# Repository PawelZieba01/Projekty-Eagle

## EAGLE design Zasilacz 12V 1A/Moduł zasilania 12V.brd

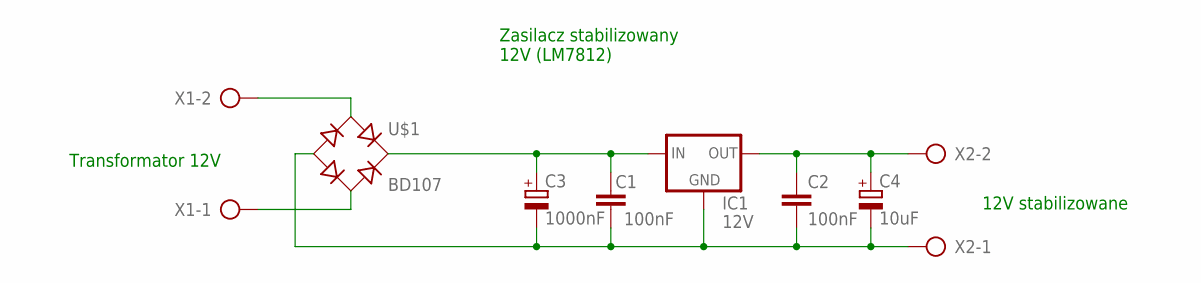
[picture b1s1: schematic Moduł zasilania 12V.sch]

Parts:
C1, C2: 100nF; C50-45-75
C3: 1000nF; E5-13
C4: 10uF; E2,5-6
IC1: 12V; 78XXS
U$1: BD107; B-DIL
X1, X2: AK300/2

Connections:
unnamed: U$1.AC1, X1.2
unnamed: U$1.AC2, X1.1
unnamed: C1.P$1 (1), C2.P$2 (2), C3.P$2 (-), C4.P$2 (-), IC1.GND, U$1.-, X2.1
unnamed: C1.P$2 (2), C3.P$1 (+), IC1.IN, U$1.+
unnamed: C2.P$1 (1), C4.P$1 (+), IC1.OUT, X2.2

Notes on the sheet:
Zasilacz stabilizowany 12V (LM7812)
Transformator 12V
12V stabilizowane

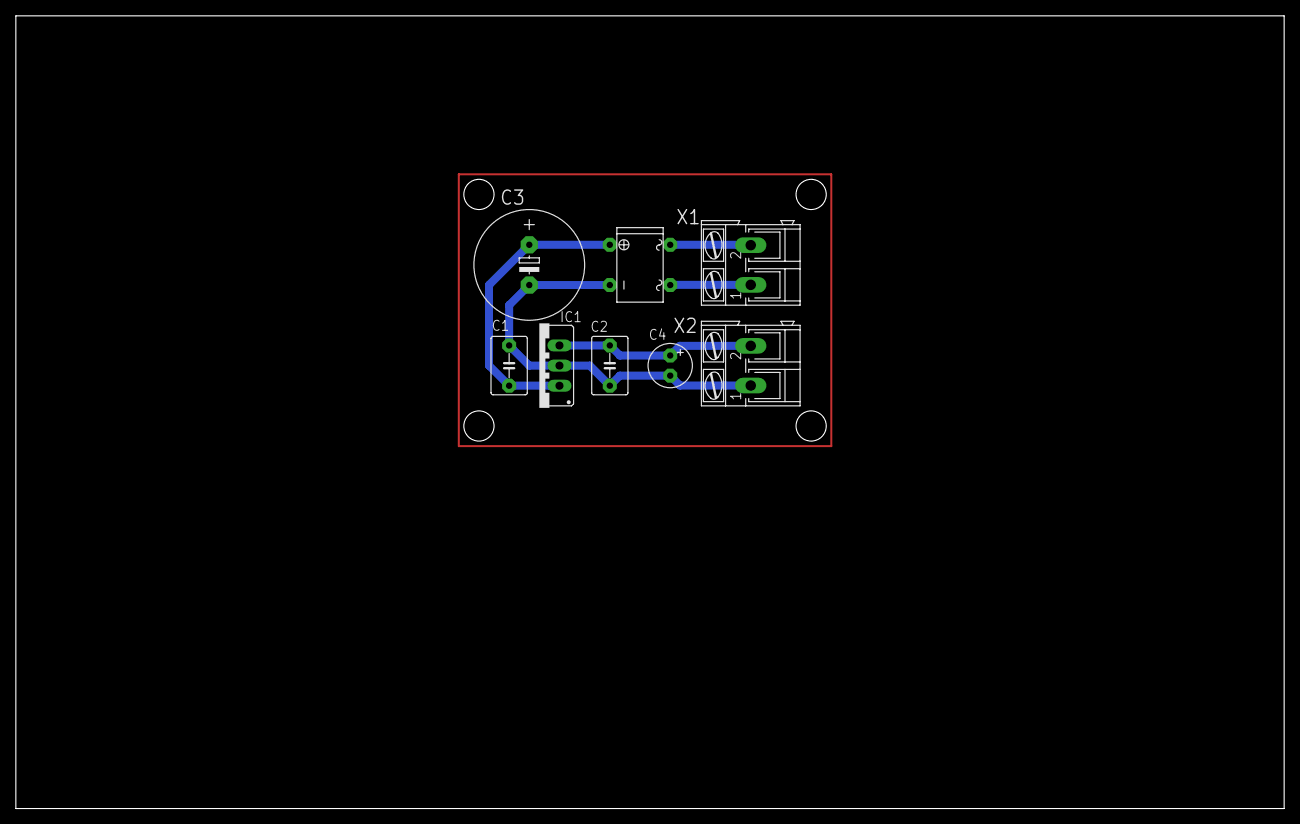
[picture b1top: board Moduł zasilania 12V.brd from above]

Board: 2 copper layers, 160.0 x 100.0 mm, 8 parts (0 on the bottom side), 5 nets.

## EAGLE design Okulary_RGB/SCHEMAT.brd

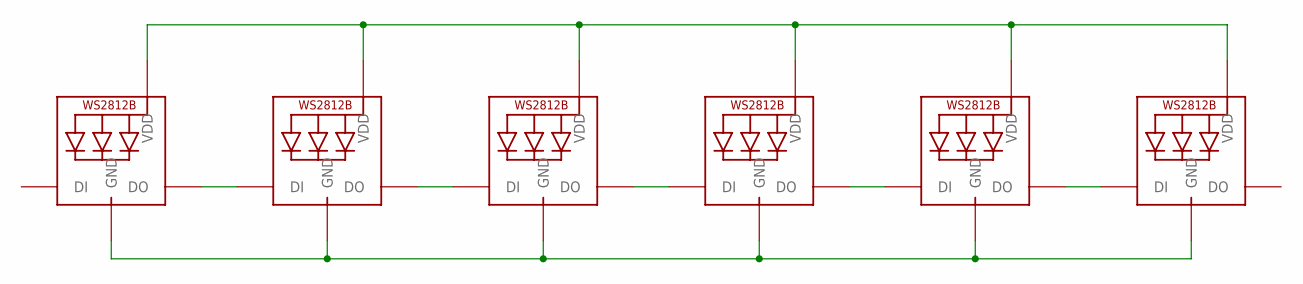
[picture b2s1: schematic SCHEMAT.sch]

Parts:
LED1, LED2, LED3, LED4, LED5, LED6: WS2812B5050; WS2812B

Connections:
unnamed: LED1.1-VDD (VDD), LED2.1-VDD (VDD), LED3.1-VDD (VDD), LED4.1-VDD (VDD), LED5.1-VDD (VDD), LED6.1-VDD (VDD)
unnamed: LED1.3-GND (GND), LED2.3-GND (GND), LED3.3-GND (GND), LED4.3-GND (GND), LED5.3-GND (GND), LED6.3-GND (GND)
unnamed: LED1.2-DOUT (DO), LED2.4-DIN (DI)
unnamed: LED2.2-DOUT (DO), LED3.4-DIN (DI)
unnamed: LED3.2-DOUT (DO), LED4.4-DIN (DI)
unnamed: LED4.2-DOUT (DO), LED5.4-DIN (DI)
unnamed: LED5.2-DOUT (DO), LED6.4-DIN (DI)

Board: 2 copper layers, 6 parts (3 on the bottom side), 7 nets, no tracks yet.

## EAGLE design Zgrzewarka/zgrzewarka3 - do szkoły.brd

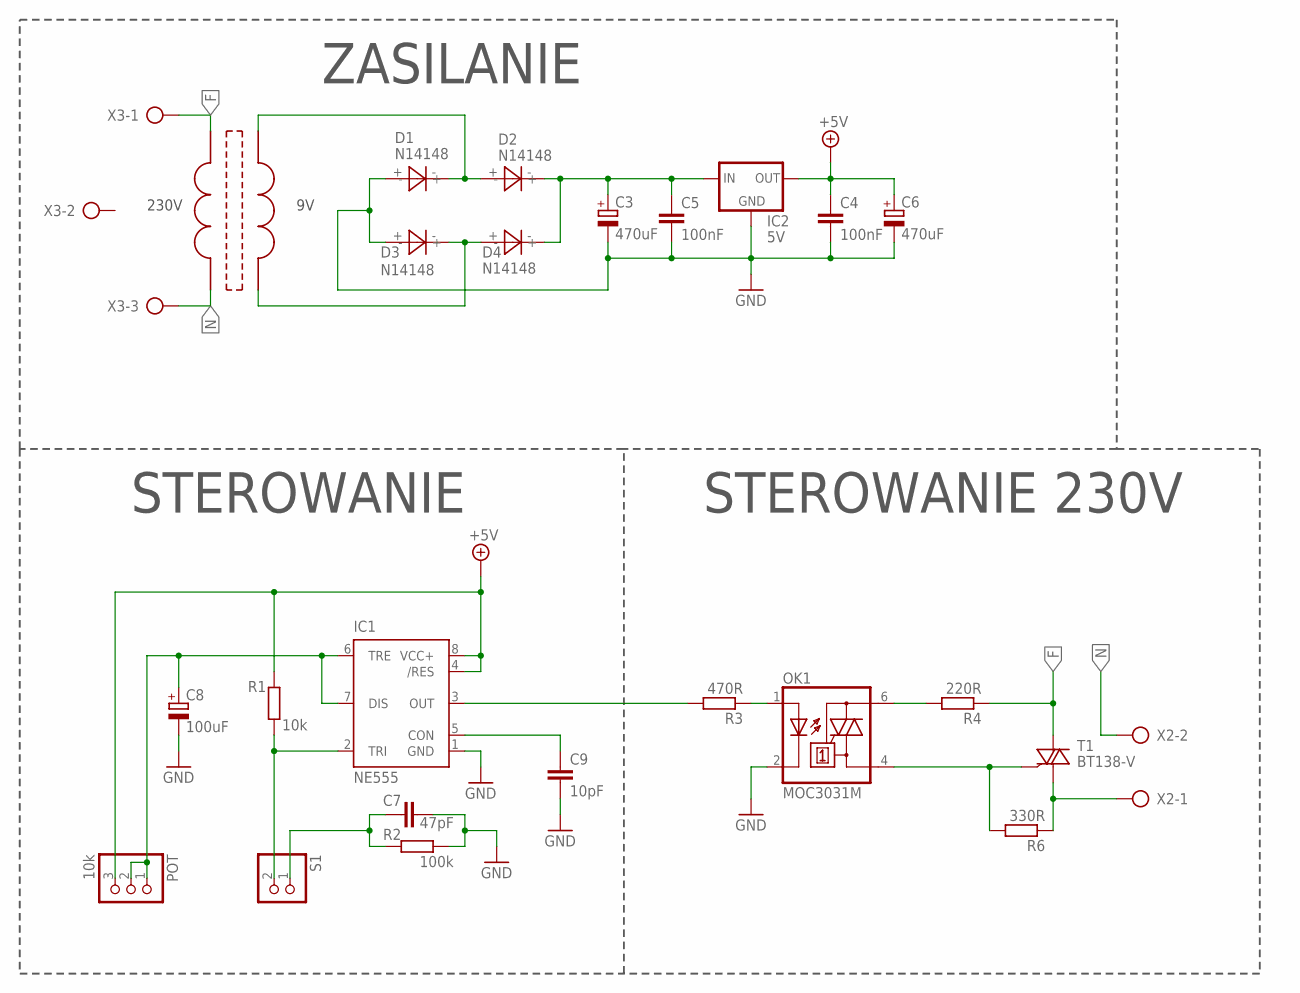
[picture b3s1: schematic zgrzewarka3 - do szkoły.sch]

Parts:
C3, C6: 470uF; C5-8,5
C4, C5: 100nF; C50-45-75
C7: 47pF; C50-45-75
C8: 100uF; C5-8,5
C9: 10pF; C50-45-75
D1, D2, D3, D4: N14148; DO35-7
IC1: NE555; DIL-08
IC2: 5V; 78LXX
OK1: MOC3031M; DIL06
POT: 10k; 1X03
R1: 10k; 204/7
R2: 100k; 204/7
R3: 470R; 204/7
R4: 220R; 204/7
R6: 330R; 204/7
S1: PINHD-1X2; 1X02
T1: BT138-V; TO220BV
U$1: TRAFO-9V; OBUDOWA1
X2: AK300/2
X3: AK300/3

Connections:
+5V: C4.P$1 (1), C6.+, IC1.4 (/RES), IC1.8 (VCC+), IC2.OUT, POT.3, R1.P$2 (2)
F: R4.P$1 (1), T1.T2 (A2), U$1.230V-1, X3.1
GND: C3.-, C4.P$2 (2), C5.P$2 (2), C6.-, C7.P$2 (2), C8.-, C9.P$2 (2), D1.+, D3.+, IC1.1 (GND), IC2.GND, OK1.2 (C), R2.P$1 (1)
N: U$1.230V-2, X2.2, X3.3
unnamed: C3.+, C5.P$1 (1), D2.-, D4.-, IC2.IN
unnamed: D1.-, D2.+, U$1.9V-1
unnamed: D3.-, D4.+, U$1.9V-2
unnamed: C9.P$1 (1), IC1.5 (CON)
unnamed: IC1.2 (TRI), R1.P$1 (1), S1.2
unnamed: IC1.3 (OUT), R3.P$2 (2)
unnamed: C7.P$1 (1), R2.P$2 (2), S1.1
unnamed: OK1.1 (A), R3.P$1 (1)
unnamed: C8.+, IC1.6 (TRE), IC1.7 (DIS), POT.1, POT.2
unnamed: OK1.6 (A2), R4.P$2 (2)
unnamed: OK1.4 (A1), R6.P$2 (2), T1.G
unnamed: R6.P$1 (1), T1.T1 (A1), X2.1

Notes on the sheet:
ZASILANIE
STEROWANIE
STEROWANIE 230V

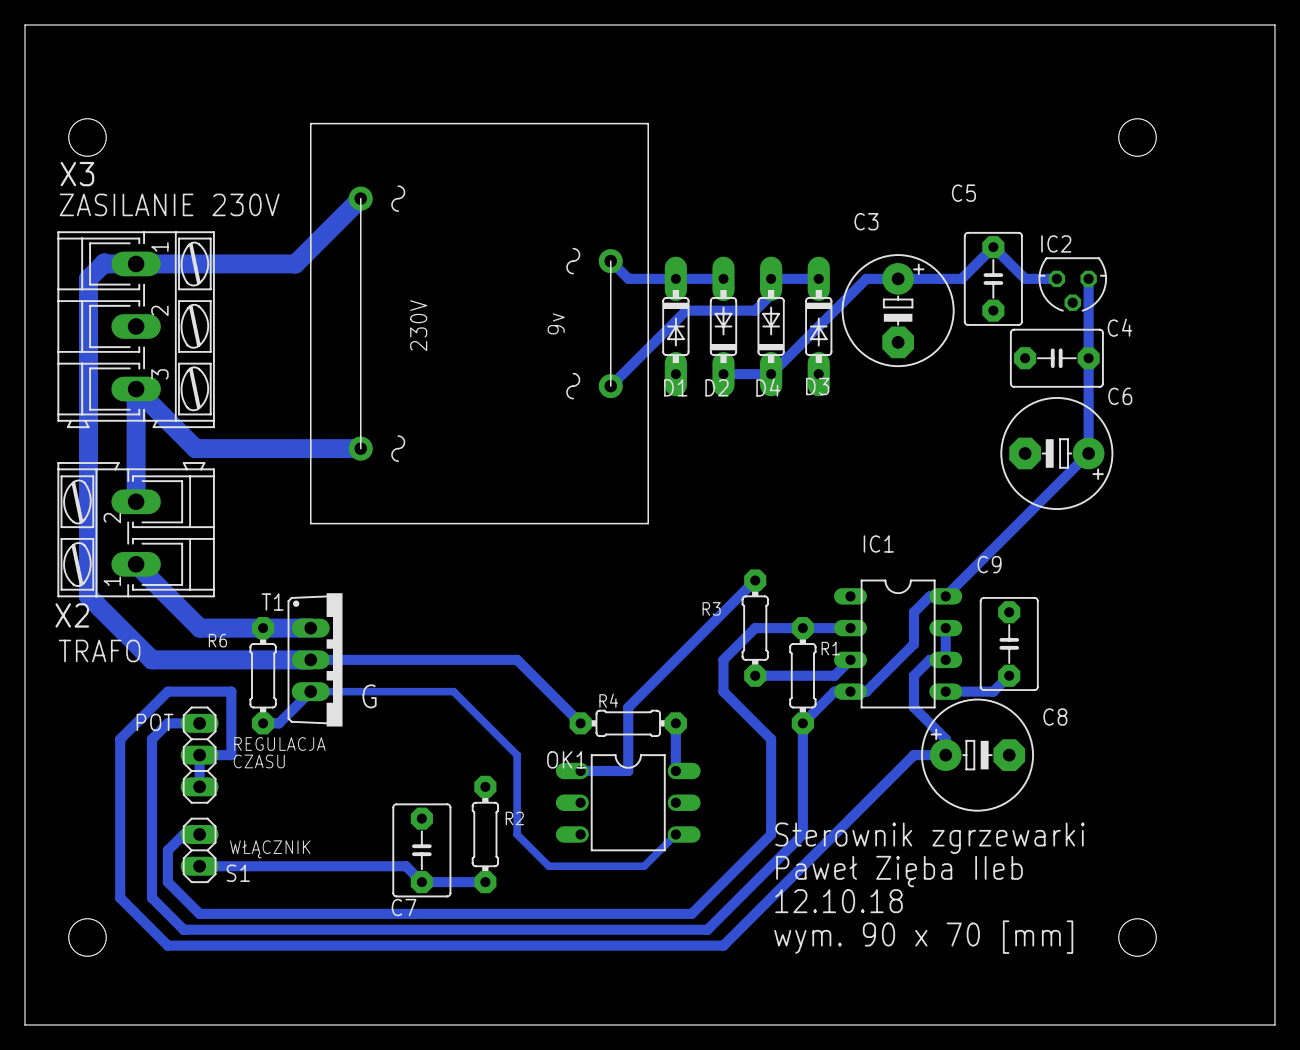
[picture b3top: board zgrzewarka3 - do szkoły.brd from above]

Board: 2 copper layers, 100.0 x 80.0 mm, 25 parts (0 on the bottom side), 16 nets.

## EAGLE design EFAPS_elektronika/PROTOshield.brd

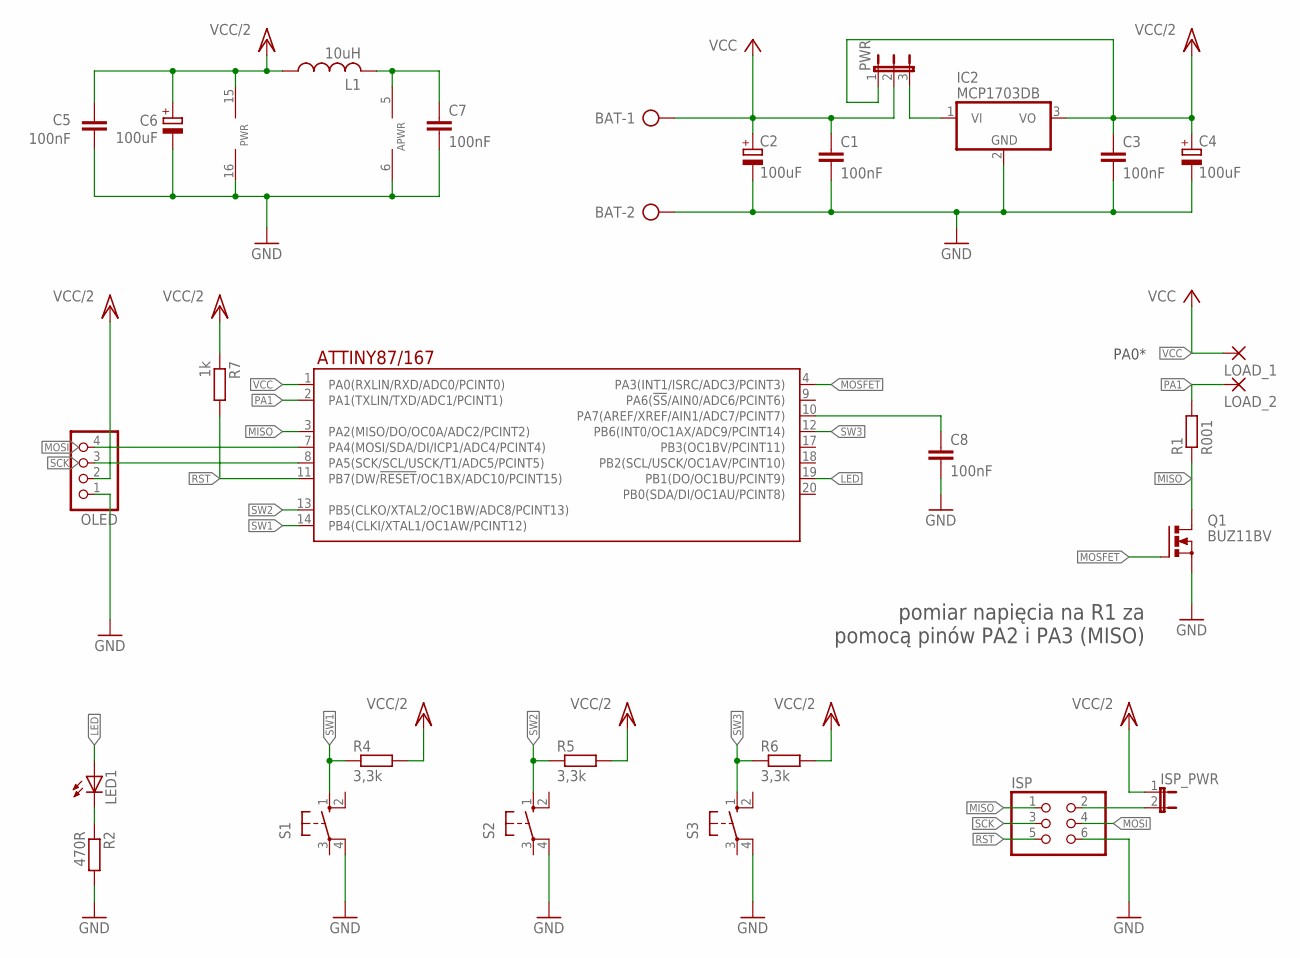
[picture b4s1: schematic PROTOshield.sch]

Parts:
BAT: AK300/2
C1, C3, C5, C7, C8: 100nF; C050-045X075
C2, C4, C6: 100uF; E3,5-8
IC2: MCP1703DB; SOT223
ISP: PINHD-2X3; 2X03
ISP_PWR: JP1E; JP1
L1: 10uH; 0207/7
LED1: LED5MM
LOAD_1, LOAD_2: 3,81/1,3
OLED: PINHD-1X4; 1X04
PWR: JP2E; JP2
Q1: BUZ11BV; TO220BV
R1: R001; R2512
R2: 470R; R1206
R4, R5, R6: 3,3k; R1206
R7: 1k; R1206
S1, S2, S3: 10-XX; B3F-10XX
U$1: ATTINY87/167; SOIC127P1032X265-20N

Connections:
GND: BAT.2, C1.2, C2.-, C3.2, C4.-, C5.2, C6.-, C7.2, C8.2, IC2.2 (GND), ISP.6, OLED.1, Q1.S, R2.2, S1.4 (P1), S2.4 (P1), S3.4 (P1), U$1.6 (AGND), U$1.16 (GND)
LED: LED1.A, U$1.19 (PB1(DO/OC1BU/PCINT9))
MISO: ISP.1, Q1.D, R1.1, U$1.3 (PA2(MISO/DO/OC0A/ADC2/PCINT2))
MOSFET: Q1.G, U$1.4 (PA3(INT1/ISRC/ADC3/PCINT3))
MOSI: ISP.4, OLED.4, U$1.7 (PA4(MOSI/SDA/DI/ICP1/ADC4/PCINT4))
unnamed: LED1.K (C), R2.1
unnamed: IC2.1 (VI), PWR.3
unnamed: ISP.2, ISP_PWR.2
unnamed: C8.1, U$1.10 (PA7(AREF/XREF/AIN1/ADC7/PCINT7))
unnamed: C7.1, L1.2, U$1.5 (AVCC)
PA1: LOAD_2.1, R1.2, U$1.2 (PA1(TXLIN/TXD/ADC1/PCINT1))
RST: ISP.5, R7.2, U$1.11 (PB7(DW/!RESET!/OC1BX/ADC10/PCINT15))
SCK: ISP.3, OLED.3, U$1.8 (PA5(SCK/SCL/USCK/T1/ADC5/PCINT5))
SW1: R4.1, S1.1 (S), U$1.14 (PB4(CLKI/XTAL1/OC1AW/PCINT12))
SW2: R5.1, S2.1 (S), U$1.13 (PB5(CLKO/XTAL2/OC1BW/ADC8/PCINT13))
SW3: R6.1, S3.1 (S), U$1.12 (PB6(INT0/OC1AX/ADC9/PCINT14))
VCC: BAT.1, C1.1, C2.+, LOAD_1.1, PWR.2, U$1.1 (PA0(RXLIN/RXD/ADC0/PCINT0))
VCC/2: C3.1, C4.+, C5.1, C6.+, IC2.3 (VO), ISP_PWR.1, L1.1, OLED.2, PWR.1, R4.2, R5.2, R6.2, R7.1, U$1.15 (VCC)

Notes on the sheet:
PA0*
pomiar napięcia na R1 za pomocą pinów PA2 i PA3 (MISO)

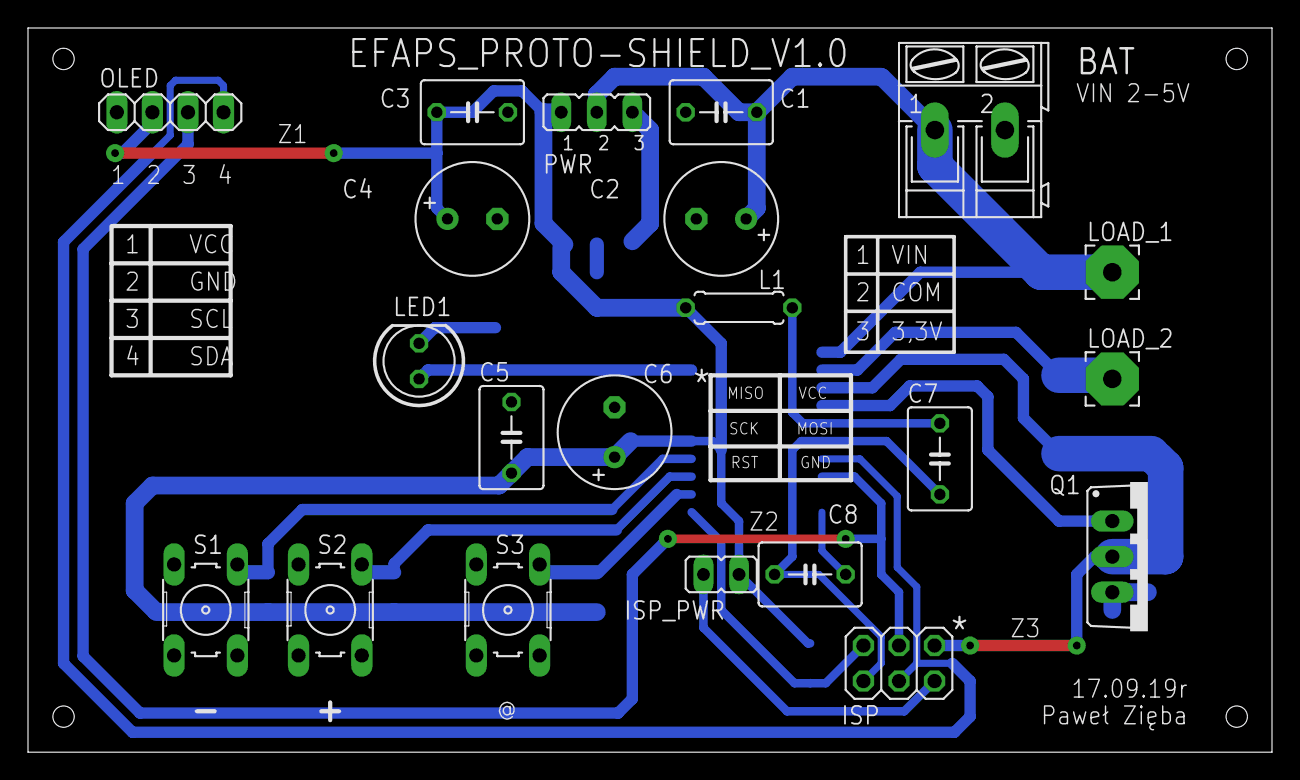
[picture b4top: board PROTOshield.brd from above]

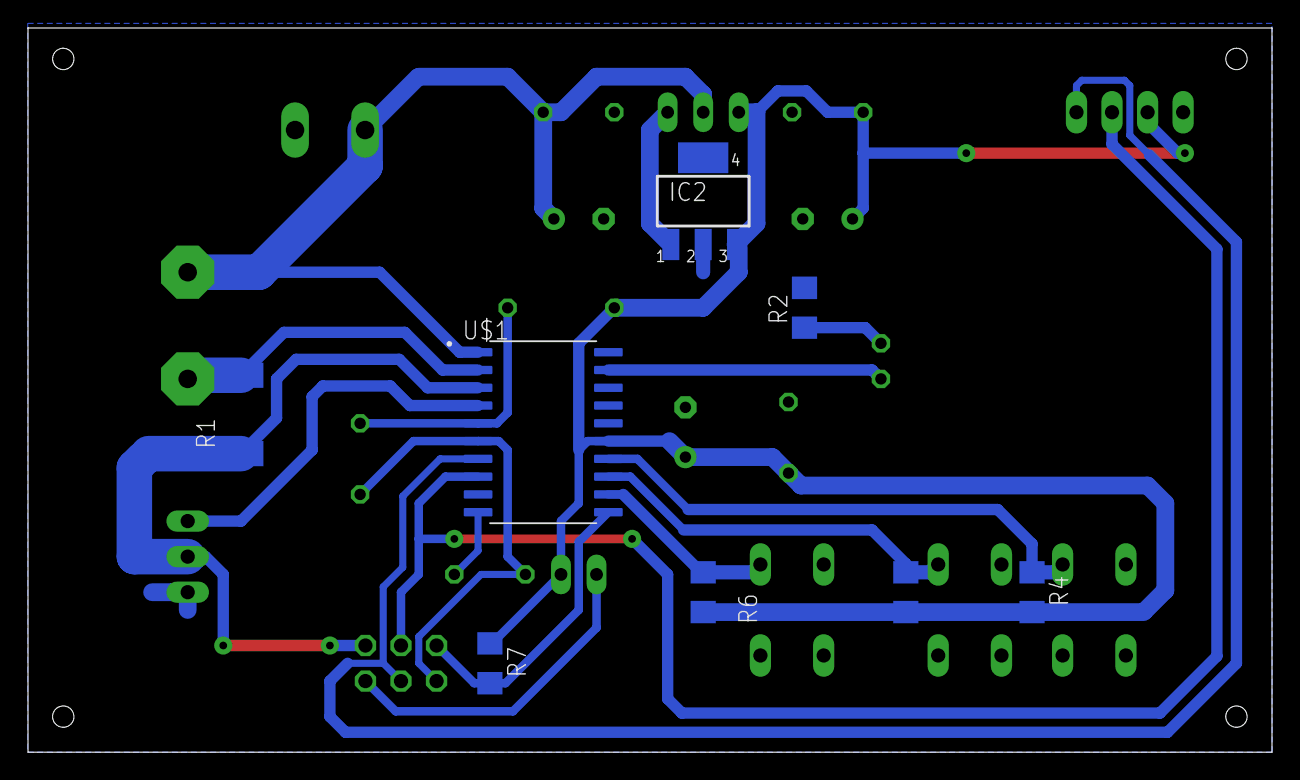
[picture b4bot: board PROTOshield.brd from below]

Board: 2 copper layers, 88.9 x 51.7 mm, 29 parts (8 on the bottom side), 18 nets.

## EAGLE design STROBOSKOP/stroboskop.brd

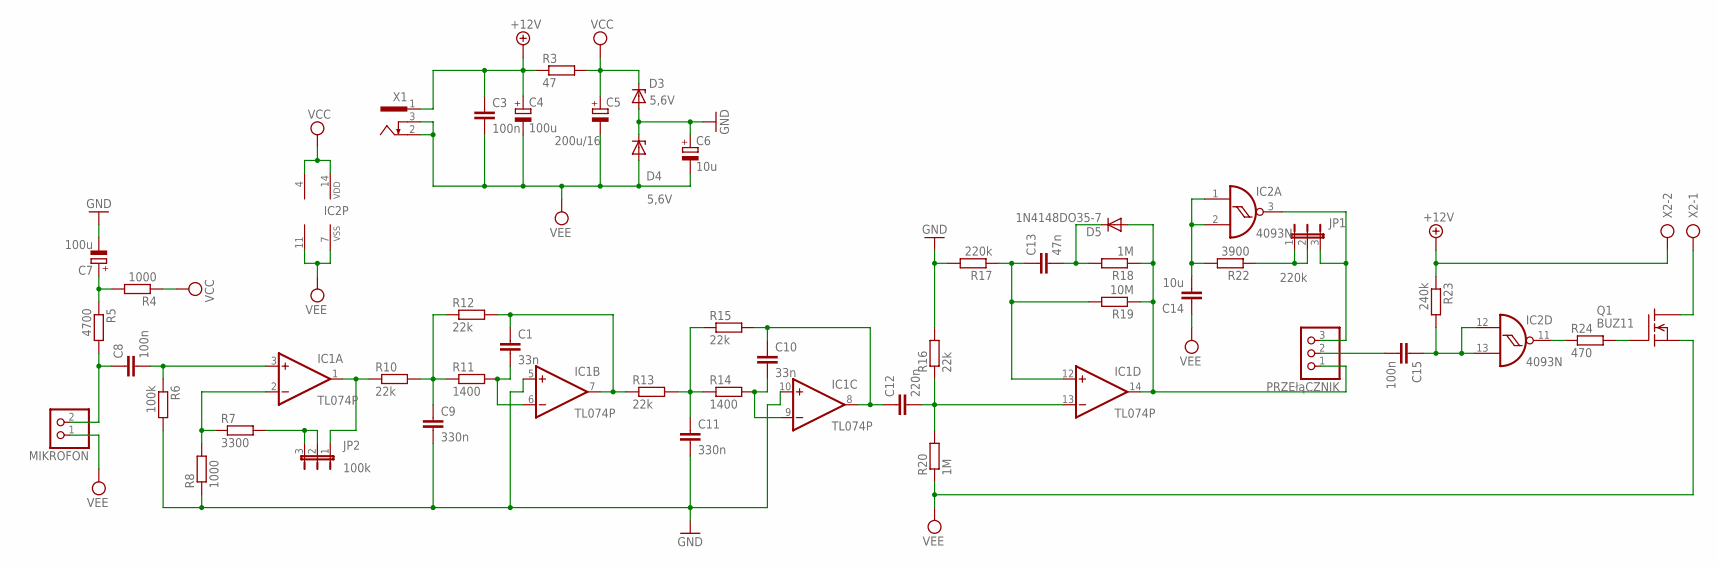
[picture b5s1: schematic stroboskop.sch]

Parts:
C1, C10: 33n; C025-025X050
C3, C8, C15: 100n; C025-025X050
C4, C7: 100u; E2,5-6E
C5: 200u/16; E2,5-6E
C6: 10u; E2,5-6E
C9, C11: 330n; C025-025X050
C12: 220n; C025-025X050
C13: 47n; C025-025X050
C14: 10u; C025-025X050
D3, D4: 5,6V; DO35Z10
D5: 1N4148DO35-7; DO35-7
IC1: TL074P; DIL14
IC2: 4093N; DIL14
JP1: 220k; JP2
JP2: 100k; JP2
MIKROFON: PINHD-1X2; 1X02
PRZEłąCZNIK: PINHD-1X3; 1X03
Q1: BUZ11; TO220
R3: 47; 0204/5
R4, R8: 1000; 0204/5
R5: 4700; 0204/5
R6: 100k; 0204/5
R7: 3300; 0204/5
R10, R12, R13, R15, R16: 22k; 0204/5
R11, R14: 1400; 0204/5
R17: 220k; 0204/5
R18, R20: 1M; 0204/5
R19: 10M; 0204/5
R22: 3900; 0204/5
R23: 240k; 0204/5
R24: 470; 0204/5
X1: 733980-62
X2: AK300/2

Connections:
+12V: C3.1, C4.+, R3.1, R23.1, X1.1, X2.2
GND: C6.+, C7.-, C9.2, C11.2, D3.A, D4.C, IC1.5 (+IN), IC1.10 (+IN), R6.2, R8.1, R16.2, R17.2
unnamed: C7.+, R4.2, R5.1
unnamed: C8.1, MIKROFON.2, R5.2
unnamed: C8.2, IC1.3 (+IN), R6.1
unnamed: C11.1, R13.2, R14.1, R15.1
unnamed: IC1.2 (-IN), R7.1, R8.2
unnamed: C10.2, IC1.9 (-IN), R14.2
unnamed: JP2.2, JP2.3, R7.2
unnamed: C10.1, C12.1, IC1.8 (OUT), R15.2
unnamed: IC1.1 (OUT), JP2.1, R10.1
unnamed: C9.1, R10.2, R11.1, R12.1
unnamed: C1.1, IC1.7 (OUT), R12.2, R13.1
unnamed: C1.2, IC1.6 (-IN), R11.2
unnamed: C12.2, IC1.13 (-IN), R16.1, R20.2
unnamed: C15.2, PRZEłąCZNIK.2
unnamed: C13.1, IC1.12 (+IN), R17.1, R19.2
unnamed: C13.2, D5.C, R18.2
unnamed: D5.A, IC1.14 (OUT), PRZEłąCZNIK.1, R18.1, R19.1
unnamed: IC2.3 (O), JP1.3, PRZEłąCZNIK.3
unnamed: C15.1, IC2.12 (I0), IC2.13 (I1), R23.2
unnamed: C14.2, IC2.1 (I0), IC2.2 (I1), R22.2
unnamed: IC2.11 (O), R24.1
unnamed: JP1.1, JP1.2, R22.1
unnamed: Q1.1 (G), R24.2
unnamed: Q1.2 (D), X2.1
VCC: C5.+, D3.C, IC1.4 (V+), IC2.14 (VDD), R3.2, R4.1
VEE: C3.2, C4.-, C5.-, C6.-, C14.1, D4.A, IC1.11 (V-), IC2.7 (VSS), MIKROFON.1, Q1.3 (S), R20.1, X1.2, X1.3

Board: 2 copper layers, 46 parts (0 on the bottom side), 28 nets, no tracks yet.

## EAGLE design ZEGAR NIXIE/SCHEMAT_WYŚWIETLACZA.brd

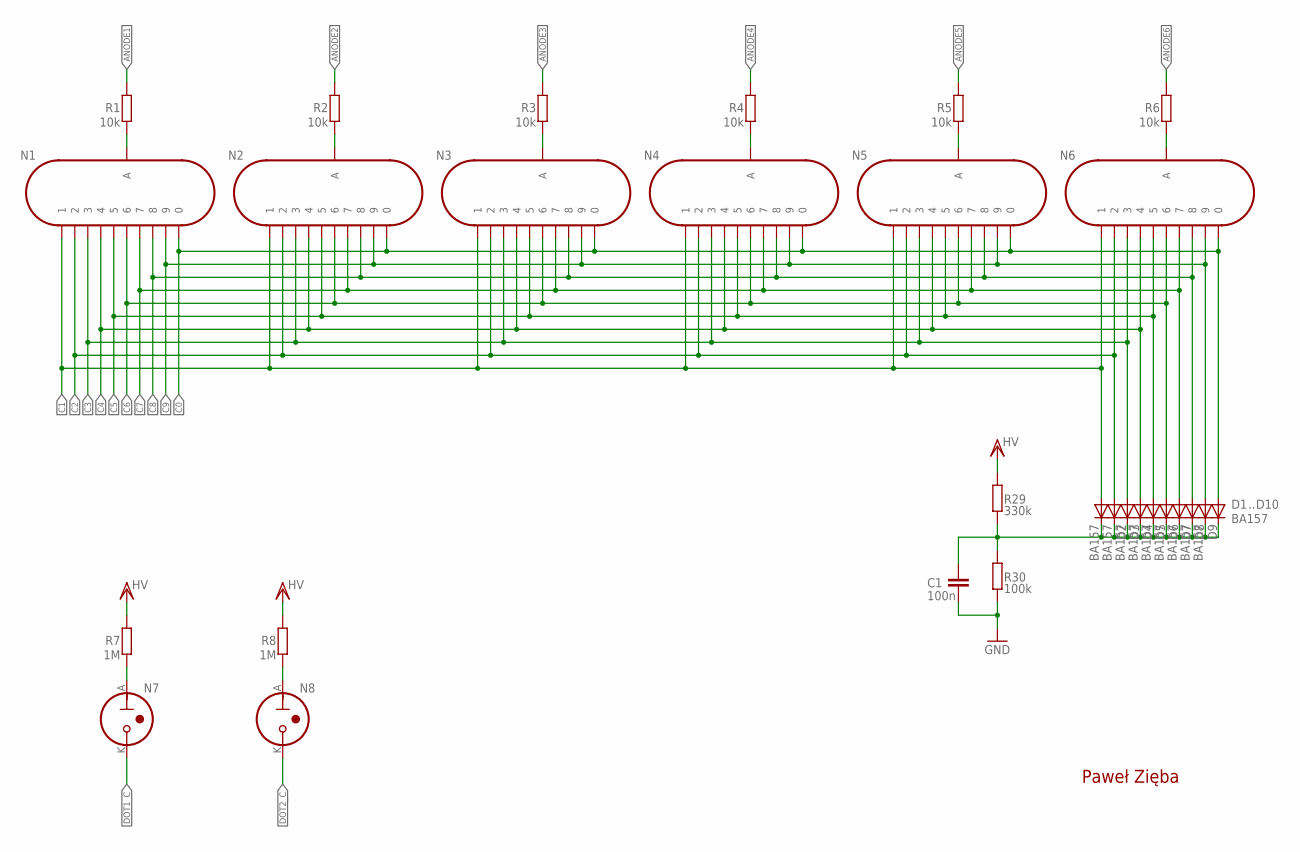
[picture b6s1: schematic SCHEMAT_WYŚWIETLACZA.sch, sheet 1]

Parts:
C1: 100n; C50-45-75
D1, D2, D3, D4, D5, D6, D7, D8, D9, D10: BA157; P1-10
N1, N2, N3, N4, N5, N6: IN-8
N7, N8: IN-3
R1, R2, R3, R4, R5, R6: 10k; 204/7
R7, R8: 1M; 204/7
R29: 330k; 204/7
R30: 100k; 204/7

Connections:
ANODE1: R1.P$2 (2); also elsewhere on the board
ANODE2: R2.P$2 (2); also elsewhere on the board
ANODE3: R3.P$2 (2); also elsewhere on the board
ANODE4: R4.P$2 (2); also elsewhere on the board
ANODE5: R5.P$2 (2); also elsewhere on the board
ANODE6: R6.P$2 (2); also elsewhere on the board
C0: D10.A, N1.0, N2.0, N3.0, N4.0, N5.0, N6.0; also elsewhere on the board
C1: D1.A, N1.1, N2.1, N3.1, N4.1, N5.1, N6.1; also elsewhere on the board
C2: D2.A, N1.2, N2.2, N3.2, N4.2, N5.2, N6.2; also elsewhere on the board
C3: D3.A, N1.3, N2.3, N3.3, N4.3, N5.3, N6.3; also elsewhere on the board
C4: D4.A, N1.4, N2.4, N3.4, N4.4, N5.4, N6.4; also elsewhere on the board
C5: D5.A, N1.5, N2.5, N3.5, N4.5, N5.5, N6.5; also elsewhere on the board
C6: D6.A, N1.6, N2.6, N3.6, N4.6, N5.6, N6.6; also elsewhere on the board
C7: D7.A, N1.7, N2.7, N3.7, N4.7, N5.7, N6.7; also elsewhere on the board
C8: D8.A, N1.8, N2.8, N3.8, N4.8, N5.8, N6.8; also elsewhere on the board
C9: D9.A, N1.9, N2.9, N3.9, N4.9, N5.9, N6.9; also elsewhere on the board
DOT1_C: N7.K; also elsewhere on the board
DOT2_C: N8.K; also elsewhere on the board
GND: C1.P$2 (2), R30.P$1 (1); also elsewhere on the board
HV: R7.P$2 (2), R8.P$2 (2), R29.P$2 (2); also elsewhere on the board
unnamed: N7.A, R7.P$1 (1)
unnamed: N8.A, R8.P$1 (1)
unnamed: N1.A, R1.P$1 (1)
unnamed: C1.P$1 (1), D1.C, D2.C, D3.C, D4.C, D5.C, D6.C, D7.C, D8.C, D9.C, D10.C, R29.P$1 (1), R30.P$2 (2)
unnamed: N2.A, R2.P$1 (1)
unnamed: N3.A, R3.P$1 (1)
unnamed: N5.A, R5.P$1 (1)
unnamed: N4.A, R4.P$1 (1)
unnamed: N6.A, R6.P$1 (1)

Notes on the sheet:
Paweł Zięba

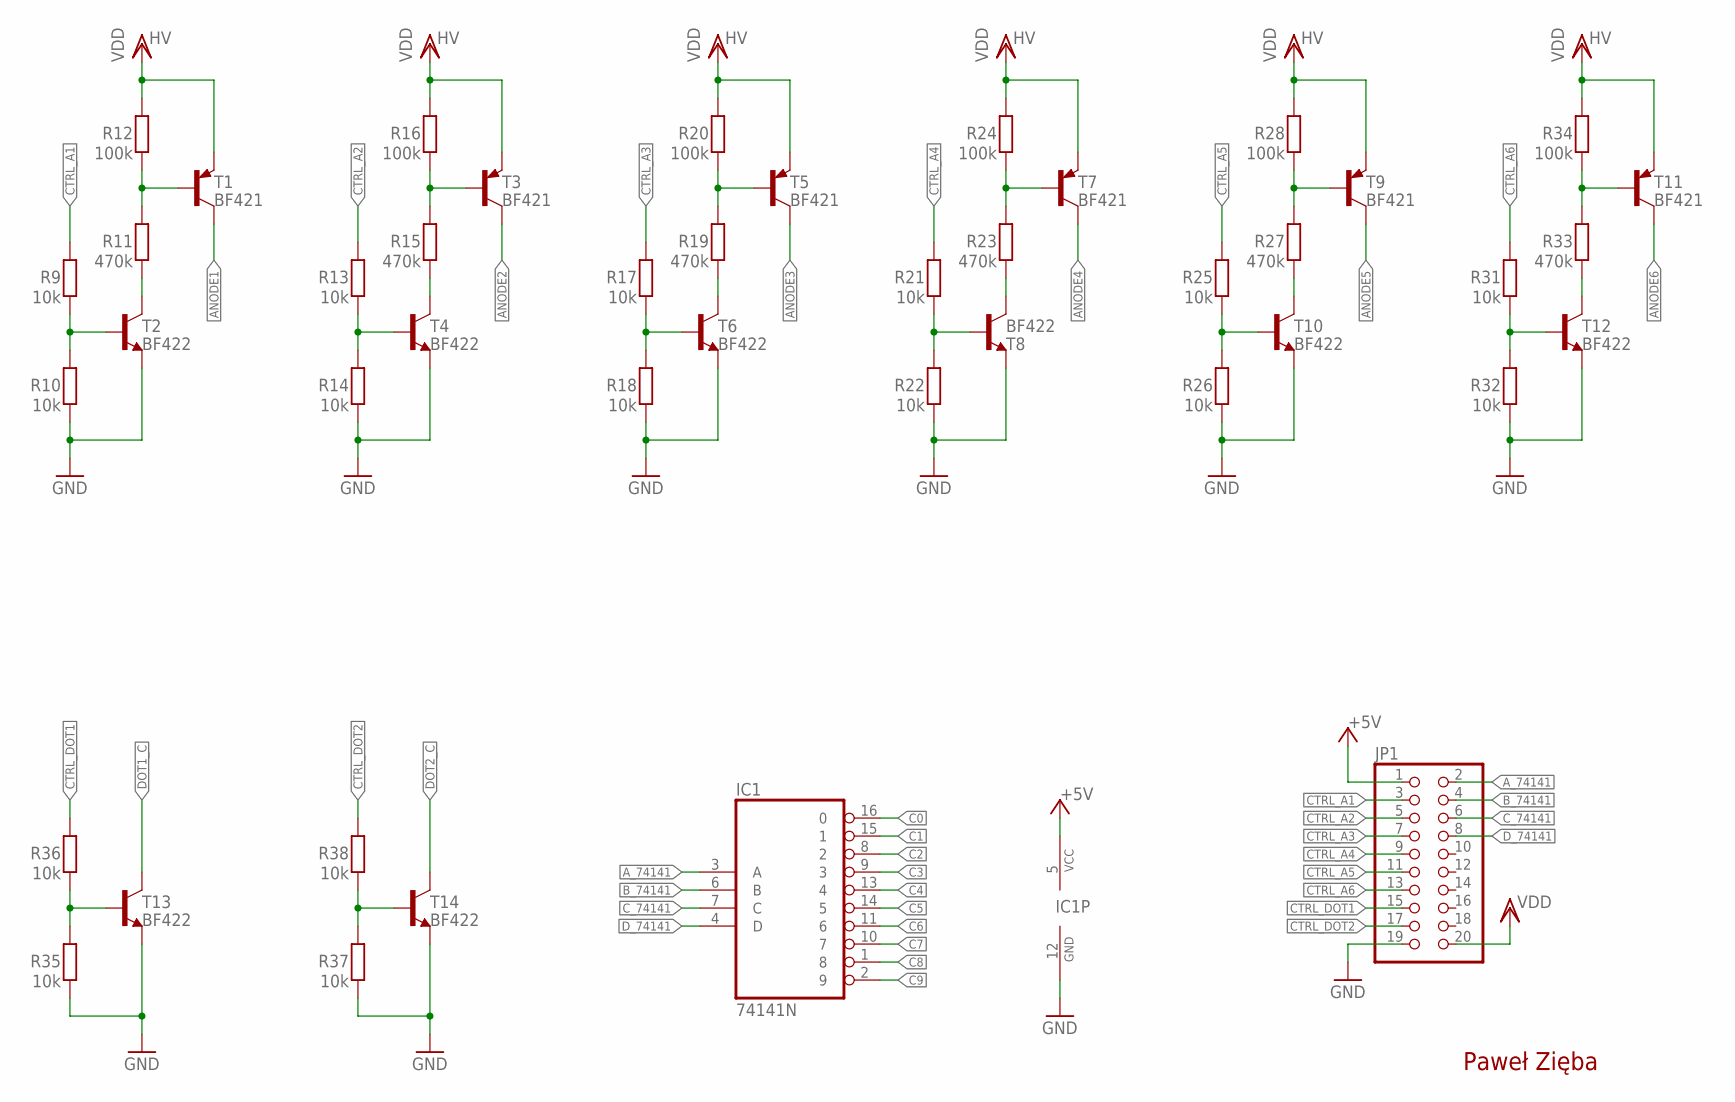
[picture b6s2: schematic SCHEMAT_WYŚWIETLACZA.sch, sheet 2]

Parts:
IC1: 74141N; DIL16
JP1: PINHD-2X10; 2X10
R9, R10, R13, R14, R17, R18, R21, R22, R25, R26, R31, R32, R35, R36, R37, R38: 10k; 204/7
R11, R15, R19, R23, R27, R33: 470k; 204/7
R12, R16, R20, R24, R28, R34: 100k; 204/7
T1, T3, T5, T7, T9, T11: BF421; TO92-BCE
T2, T4, T6, T8, T10, T12, T13, T14: BF422; TO92-BCE

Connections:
+5V: IC1.5 (VCC), JP1.1
ANODE1: T1.C; also elsewhere on the board
ANODE2: T3.C; also elsewhere on the board
ANODE3: T5.C; also elsewhere on the board
ANODE4: T7.C; also elsewhere on the board
ANODE5: T9.C; also elsewhere on the board
ANODE6: T11.C; also elsewhere on the board
A_74141: IC1.3 (A), JP1.2
B_74141: IC1.6 (B), JP1.4
C0: IC1.16 (0); also elsewhere on the board
C1: IC1.15 (1); also elsewhere on the board
C2: IC1.8 (2); also elsewhere on the board
C3: IC1.9 (3); also elsewhere on the board
C4: IC1.13 (4); also elsewhere on the board
C5: IC1.14 (5); also elsewhere on the board
C6: IC1.11 (6); also elsewhere on the board
C7: IC1.10 (7); also elsewhere on the board
C8: IC1.1 (8); also elsewhere on the board
C9: IC1.2 (9); also elsewhere on the board
CTRL_A1: JP1.3, R9.P$2 (2)
CTRL_A2: JP1.5, R13.P$2 (2)
CTRL_A3: JP1.7, R17.P$2 (2)
CTRL_A4: JP1.9, R21.P$2 (2)
CTRL_A5: JP1.11, R25.P$2 (2)
CTRL_A6: JP1.13, R31.P$2 (2)
CTRL_DOT1: JP1.15, R36.P$2 (2)
CTRL_DOT2: JP1.17, R38.P$2 (2)
C_74141: IC1.7 (C), JP1.6
DOT1_C: T13.C; also elsewhere on the board
DOT2_C: T14.C; also elsewhere on the board
D_74141: IC1.4 (D), JP1.8
GND: IC1.12 (GND), JP1.19, R10.P$1 (1), R14.P$1 (1), R18.P$1 (1), R22.P$1 (1), R26.P$1 (1), R32.P$1 (1), R35.P$1 (1), R37.P$1 (1), T2.E, T4.E, T6.E, T8.E, T10.E, T12.E, T13.E, T14.E; also elsewhere on the board
HV: JP1.20, R12.P$2 (2), R16.P$2 (2), R20.P$2 (2), R24.P$2 (2), R28.P$2 (2), R34.P$2 (2), T1.E, T3.E, T5.E, T7.E, T9.E, T11.E; also elsewhere on the board
unnamed: R9.P$1 (1), R10.P$2 (2), T2.B
unnamed: R11.P$1 (1), T2.C
unnamed: R11.P$2 (2), R12.P$1 (1), T1.B
unnamed: R13.P$1 (1), R14.P$2 (2), T4.B
unnamed: R15.P$1 (1), T4.C
unnamed: R15.P$2 (2), R16.P$1 (1), T3.B
unnamed: R17.P$1 (1), R18.P$2 (2), T6.B
unnamed: R19.P$1 (1), T6.C
unnamed: R19.P$2 (2), R20.P$1 (1), T5.B
unnamed: R21.P$1 (1), R22.P$2 (2), T8.B
unnamed: R23.P$1 (1), T8.C
unnamed: R23.P$2 (2), R24.P$1 (1), T7.B
unnamed: R25.P$1 (1), R26.P$2 (2), T10.B
unnamed: R27.P$1 (1), T10.C
unnamed: R27.P$2 (2), R28.P$1 (1), T9.B
unnamed: R31.P$1 (1), R32.P$2 (2), T12.B
unnamed: R33.P$1 (1), T12.C
unnamed: R33.P$2 (2), R34.P$1 (1), T11.B
unnamed: R35.P$2 (2), R36.P$1 (1), T13.B
unnamed: R37.P$2 (2), R38.P$1 (1), T14.B

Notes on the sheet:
Paweł Zięba

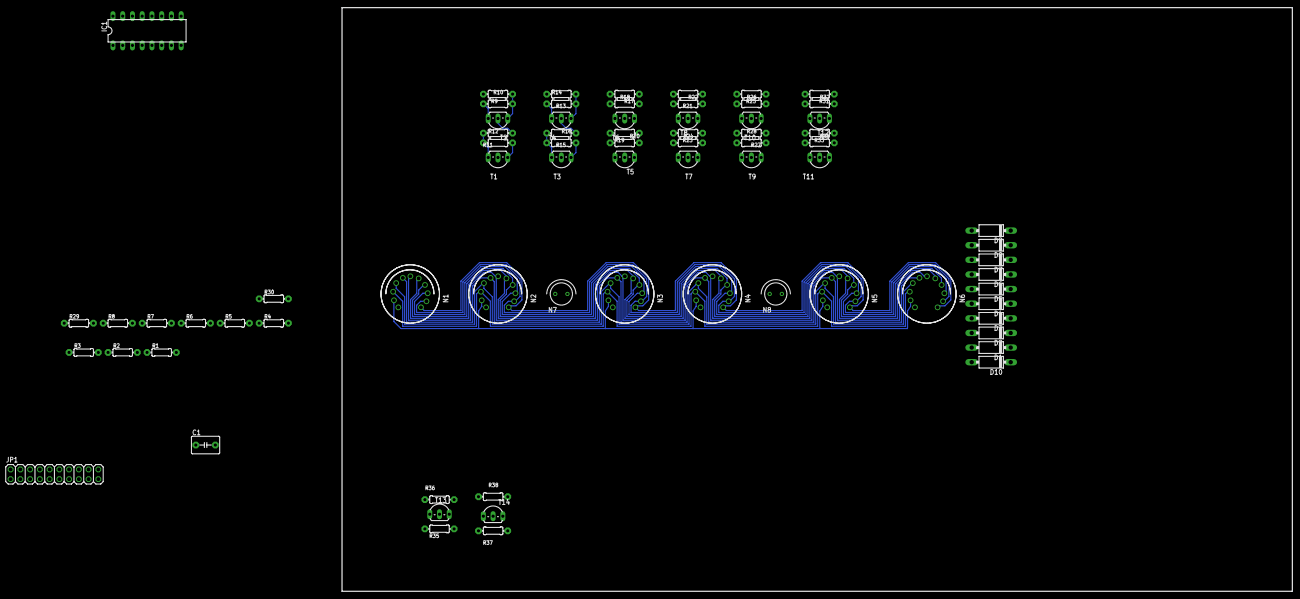
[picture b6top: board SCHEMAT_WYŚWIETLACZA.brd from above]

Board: 2 copper layers, 247.6 x 152.1 mm, 73 parts (0 on the bottom side), 62 nets.

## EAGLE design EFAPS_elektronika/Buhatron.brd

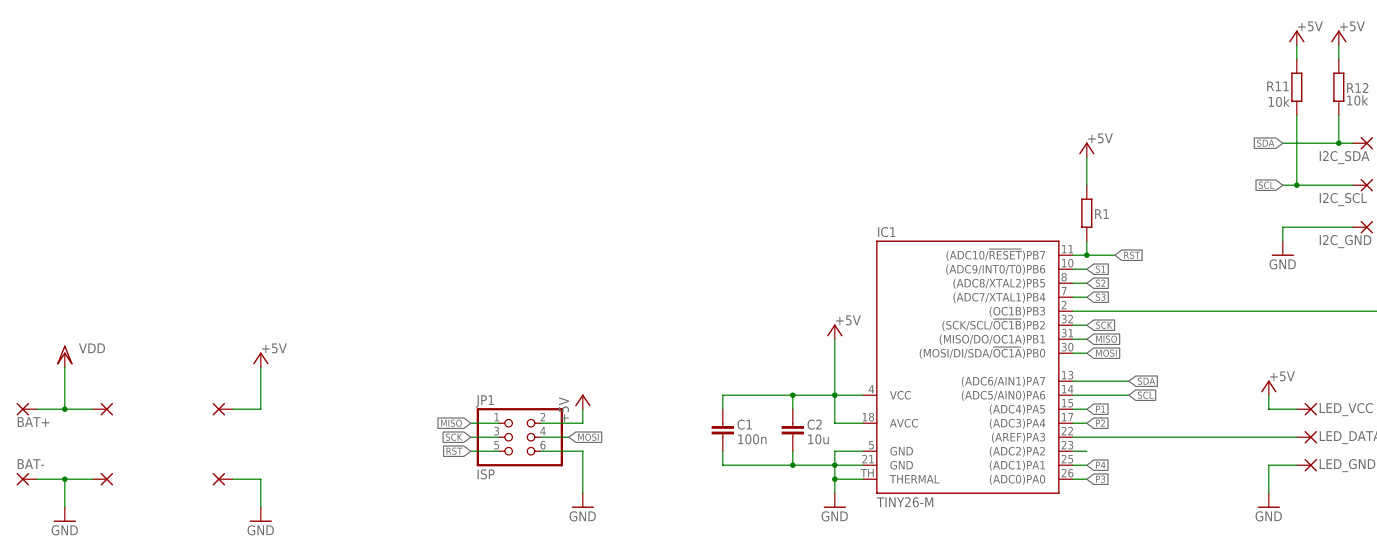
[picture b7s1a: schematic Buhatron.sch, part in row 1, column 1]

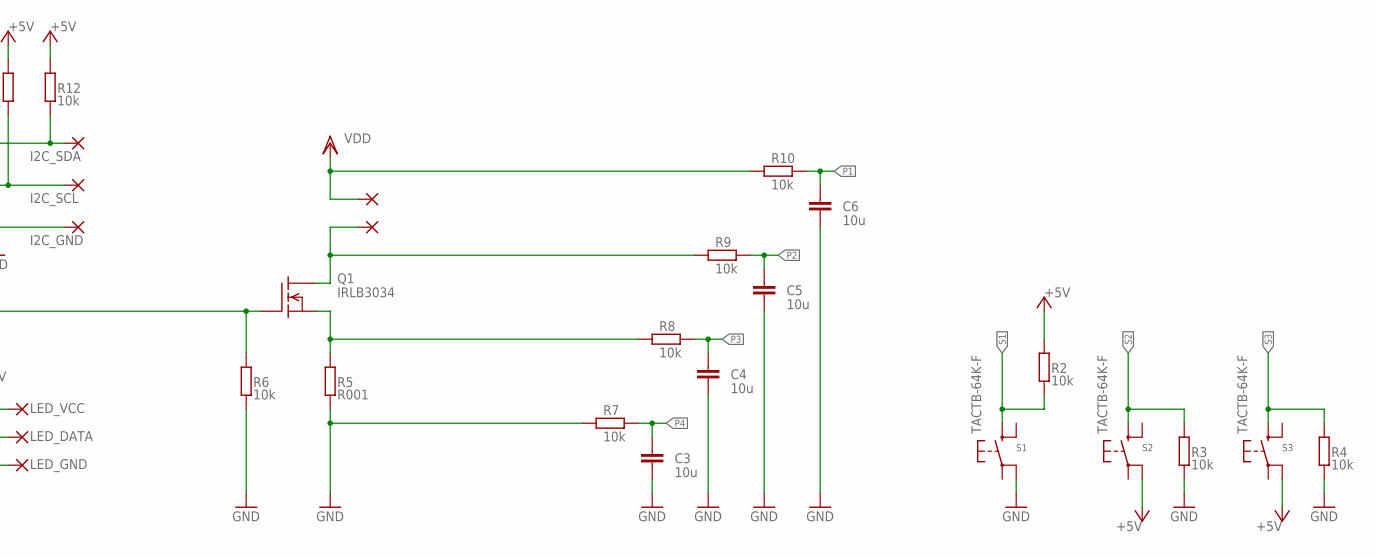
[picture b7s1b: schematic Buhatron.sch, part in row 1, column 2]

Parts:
BAT+: 3,81/1,4
BAT-: 3,81/1,4
C1: 100n; C0805
C2, C3, C4, C5, C6: 10u; C0805
HEATER-1, HEATER-2: 3,81/1,4
I2C_GND, I2C_SCL, I2C_SDA: SMD2; SMD1,27-2,54
IC1: TINY26-M; MLF32-TH
JP1: ISP; 2X03
LED_DATA: SMD2; SMD1,27-2,54
LED_GND: SMD2; SMD1,27-2,54
LED_VCC: SMD2; SMD1,27-2,54
Q1: IRLB3034; TO220
R1: R-EU_M0805; M0805
R2, R3, R4, R6, R7, R8, R9, R10, R11, R12: 10k; M0805
R5: R001; R2512
S1, S2, S3: TACTB-64K-F; 8-4.8_SMD
STEP-UP_GND: 3,81/1,4
STEP_UP+: 3,81/1,4
STEP_UP-: 3,81/1,4
STEP_UP_VCC: 3,81/1,4

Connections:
+5V: C1.1, C2.1, IC1.4 (VCC), IC1.18 (AVCC), JP1.2, LED_VCC.1, R1.2, R2.2, R11.2, R12.2, S2.P$4, S3.P$4, STEP_UP+.1
GND: BAT-.1, C1.2, C2.2, C3.2, C4.2, C5.2, C6.2, I2C_GND.1, IC1.5 (GND), IC1.21 (GND), IC1.TH (THERMAL), JP1.6, LED_GND.1, R3.1, R4.1, R5.1, R6.1, R7.1, S1.P$4, STEP-UP_GND.1, STEP_UP-.1
LED_D: IC1.22 ((AREF)PA3), LED_DATA.1
MISO: IC1.31 ((MISO/DO/OC1A)PB1), JP1.1
MOSI: IC1.30 ((MOSI/DI/SDA/!OC1A!)PB0), JP1.4
unnamed: IC1.2 ((OC1B)PB3), Q1.1 (G), R6.2
unnamed: Q1.3 (S), R5.2, R8.1
unnamed: HEATER-2.1, Q1.2 (D), R9.1
P1: C6.1, IC1.15 ((ADC4)PA5), R10.2
P2: C5.1, IC1.17 ((ADC3)PA4), R9.2
P3: C4.1, IC1.26 ((ADC0)PA0), R8.2
P4: C3.1, IC1.25 ((ADC1)PA1), R7.2
RST: IC1.11 ((ADC10/!RESET!)PB7), JP1.5, R1.1
S1: IC1.10 ((ADC9/INT0/T0)PB6), R2.1, S1.P$1
S2: IC1.8 ((ADC8/XTAL2)PB5), R3.2, S2.P$1
S3: IC1.7 ((ADC7/XTAL1)PB4), R4.2, S3.P$1
SCK: IC1.32 ((SCK/SCL/!OC1B!)PB2), JP1.3
SCL: I2C_SCL.1, IC1.14 ((ADC5/AIN0)PA6), R11.1
SDA: I2C_SDA.1, IC1.13 ((ADC6/AIN1)PA7), R12.1
VDD: BAT+.1, HEATER-1.1, R10.1, STEP_UP_VCC.1

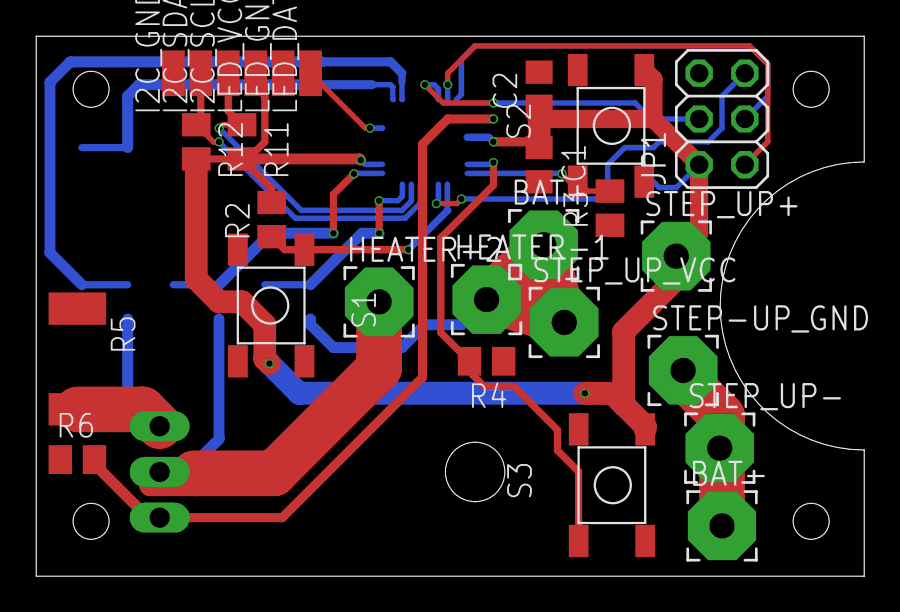
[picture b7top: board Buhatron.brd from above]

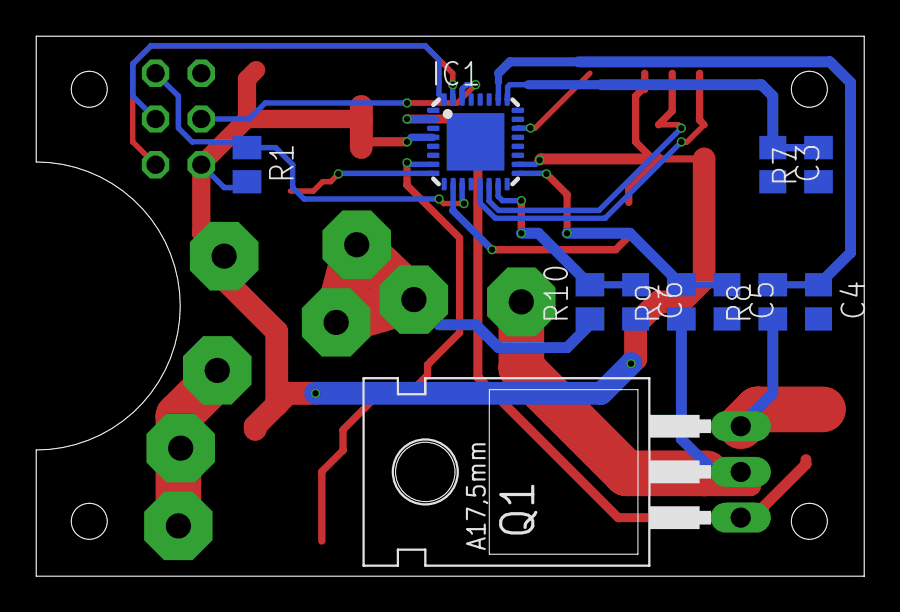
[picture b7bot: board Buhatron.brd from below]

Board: 2 copper layers, 46.0 x 30.0 mm, 38 parts (11 on the bottom side), 20 nets.
